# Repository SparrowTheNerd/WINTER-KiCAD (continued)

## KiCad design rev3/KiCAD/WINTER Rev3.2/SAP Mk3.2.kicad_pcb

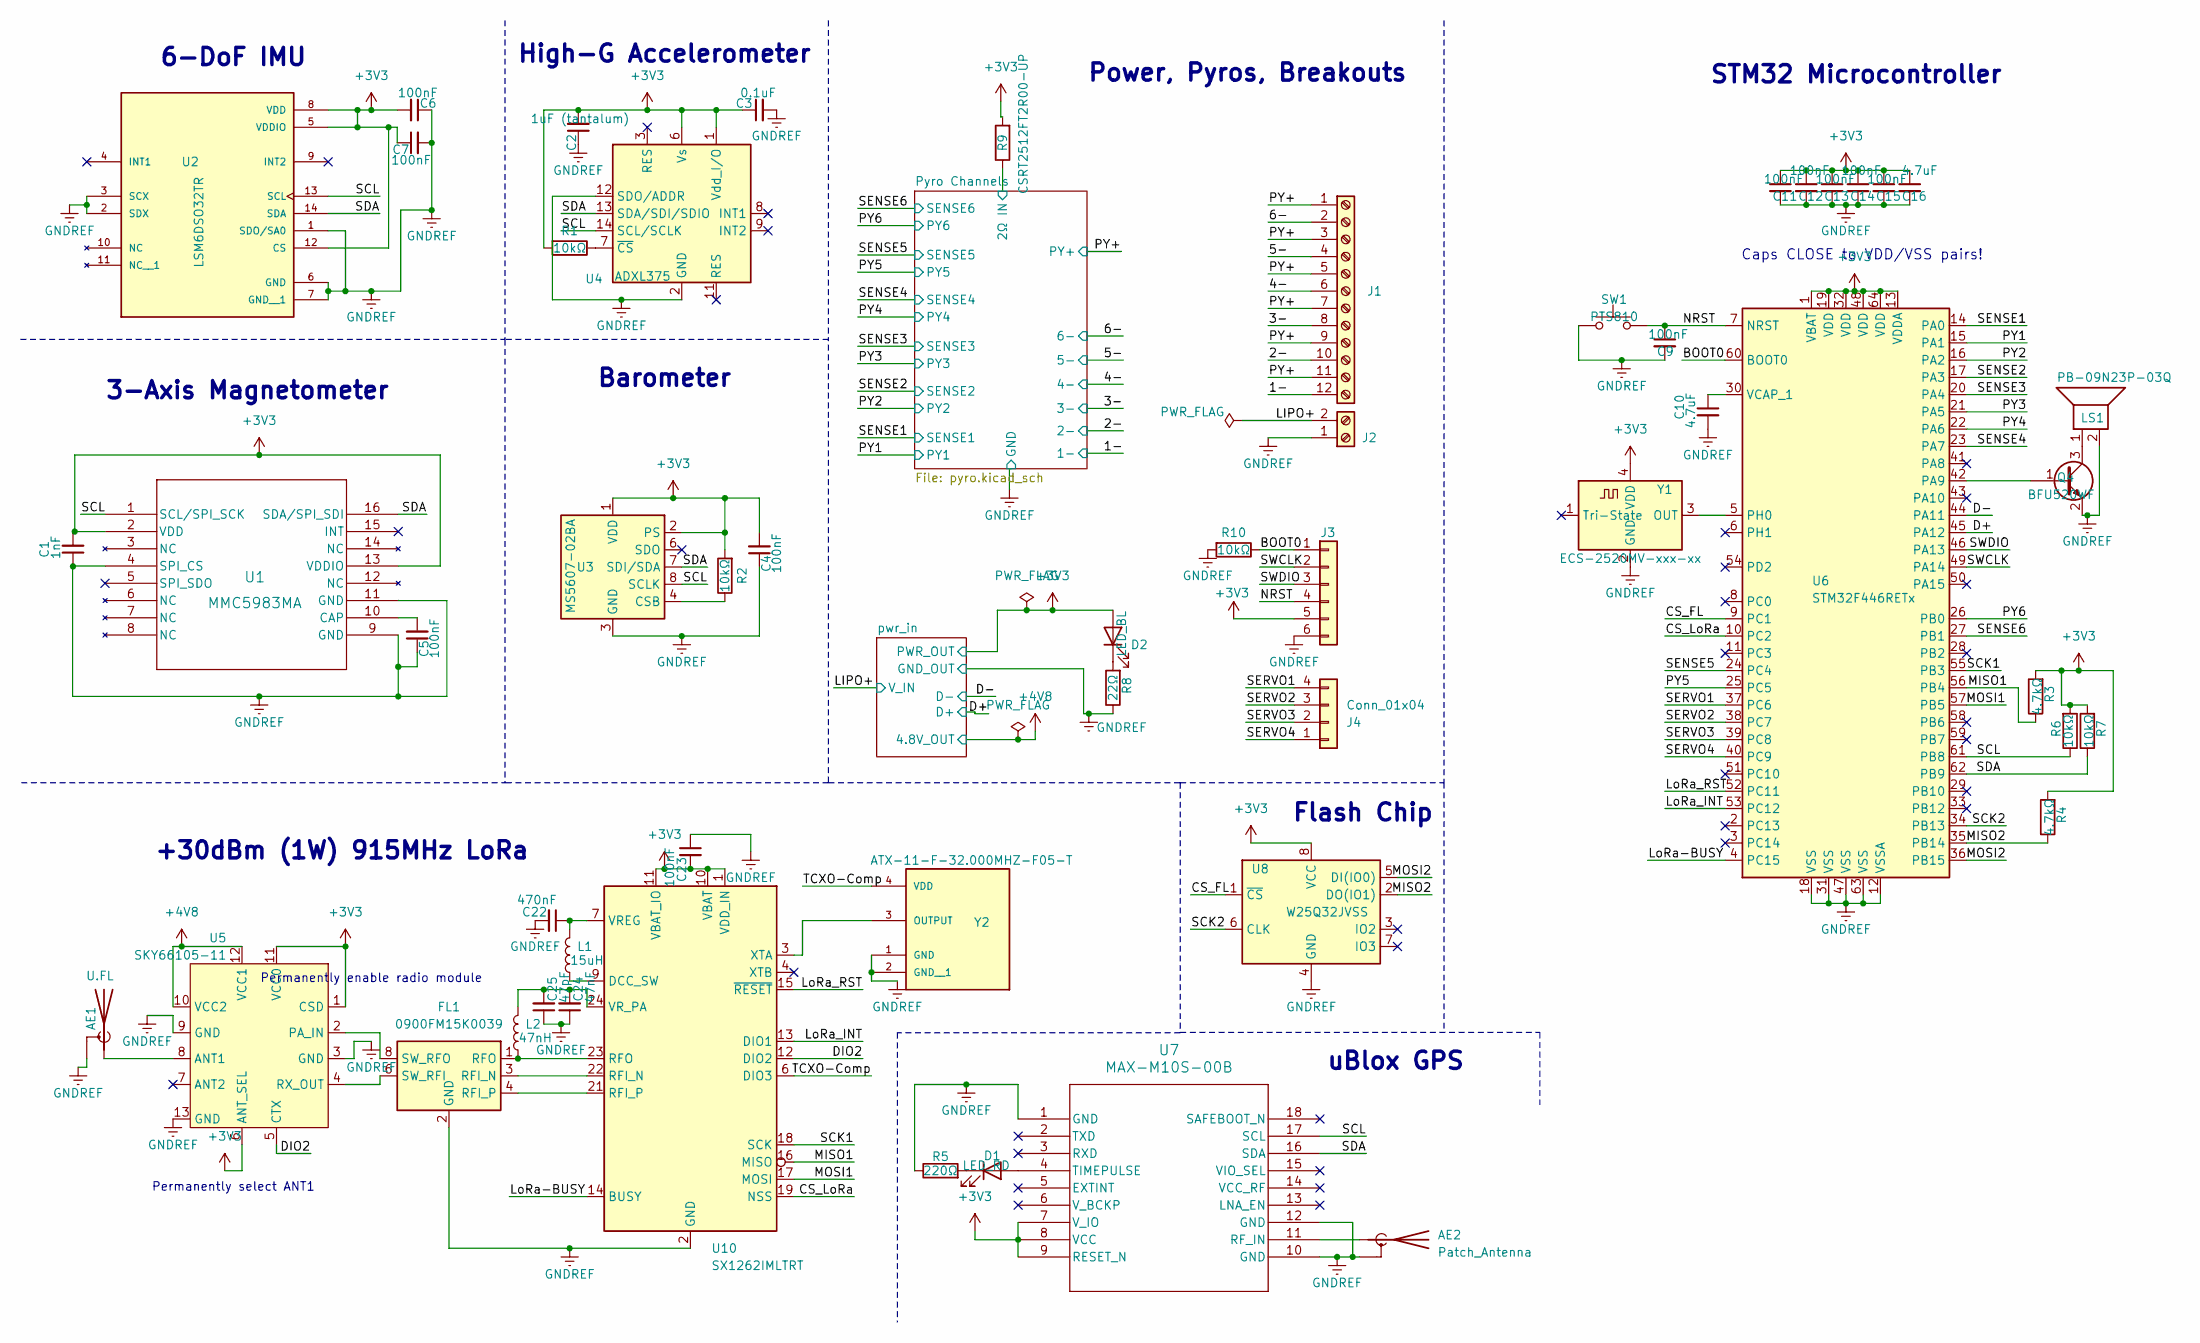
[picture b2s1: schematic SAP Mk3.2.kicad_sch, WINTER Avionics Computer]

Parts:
AE1: U.FL; U.FL_Molex_MCRF_73412-0110_Vertical
AE2: Patch_Antenna; TAOGLAS SGGP.12.4.A.02
C1: 1nF; C_0603_1608Metric
C2: 1uF (tantalum); C_0603_1608Metric
C3: 0.1uF; C_0603_1608Metric
C4, C5, C6, C7, C9, C11, C12, C13, C14, C15, C23: 100nF; C_0603_1608Metric
C10, C16: 4.7uF; C_0603_1608Metric
C22: 470nF; C_0603_1608Metric
C24: 47nF; C_0201_0603Metric
C25: 47pF; C_0201_0603Metric
D1: LED_RD; LED_0603_1608Metric
D2: LED_BL; LED_0603_1608Metric
FL1: 0900FM15K0039; Balun_Johanson_0900FM15K0039
J1: Screw_Terminal_01x12; TerminalBlock_Phoenix_MPT-0,5-12-2.54_1x12_P2.54mm_Horizont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
J2: Screw_Terminal_01x02; PinHeader_1x02_P2.54mm_Vertical
J3: Conn_01x06; PinHeader_1x06_P2.54mm_Vertical
J4: Conn_01x04; PinHeader_1x04_P2.54mm_Vertical
L1: 15uH; L_0805_2012Metric
L2: 47nH; L_0402_1005Metric
LS1: PB-09N23P-03Q; MagneticBuzzer_ProSignal_ABT-410-RC
Q4: BFU520WF; SOT-323_SC-70
R1, R2, R6, R7, R10: 10kΩ; R_0603_1608Metric
R3, R4: 4.7kΩ; R_0603_1608Metric
R5: 220Ω; R_0603_1608Metric
R8: 22Ω; R_0603_1608Metric
R9: CSRT2512FT2R00-UP; R_2512_6332Metric
SW1: PTS810; SW_SPST_PTS810
U1: MMC5983MA; MMC5983MA_MEM
U2: LSM6DSO32TR; PARTREV 1
U3: MS5607-02BA; LGA-8_3x5mm_P1.25mm
U4: ADXL375; LGA-14_3x5mm_P0.8mm_LayoutBorder1x6y
U5: SKY66105-11
U6: STM32F446RETx; LQFP-64_10x10mm_P0.5mm
U7: MAX-M10S-00B
U8: W25Q32JVSS; SOIC-8_5.23x5.23mm_P1.27mm
U10: SX1262IMLTRT; QFN-24-1EP_4x4mm_P0.5mm_EP2.6x2.6mm
Y1: ECS-2520MV-xxx-xx; Oscillator_SMD_ECS_2520MV-xxx-xx-4Pin_2.5x2.0mm
Y2: ATX-11-F-32.000MHZ-F05-T; OSC_ATX-11-F-32.000MHZ-F05-T; PARTREV 11-11-20

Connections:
+3V3: C1.2, C2.2, C3.1, C4.2, C6.2, C7.1, C11.1, C12.1, C13.1, C14.1, C15.1, C16.1, C23.2, D2.2 (A), J3.5, R1.2, R2.2, R3.2, R4.2, R6.2, R7.2, R9.2, U1.2 (VDD), U1.13 (VDDIO), U2.5 (VDDIO), U2.8 (VDD), U2.12 (CS), U3.1 (VDD), U3.2 (PS), U4.1 (Vdd_I/O), U4.6 (Vs), U5.1 (CSD), U5.6 (ANT_SEL), U5.11 (VCC0), U6.1 (VBAT), U6.13 (VDDA), U6.19 (VDD), U6.32 (VDD), U6.48 (VDD), U6.64 (VDD), U7.7 (V_IO), U7.8 (VCC), U7.9 (RESET_N), U8.8 (VCC), U10.1 (VDD_IN), U10.10 (VBAT), U10.11 (VBAT_IO), Y1.4 (VDD); also elsewhere on the board
+4V8: U5.10 (VCC2), U5.12 (VCC1); also elsewhere on the board
/1-: J1.12; also elsewhere on the board
/2-: J1.10; also elsewhere on the board
/3-: J1.8; also elsewhere on the board
/4-: J1.6; also elsewhere on the board
/5-: J1.4; also elsewhere on the board
/6-: J1.2; also elsewhere on the board
/BOOT0: J3.1, R10.1, U6.60 (BOOT0)
/CS_FL: U6.9 (PC1), U8.1 (~CS)
/CS_LoRa: U6.10 (PC2), U10.19 (NSS)
/D+: U6.45 (PA12); also elsewhere on the board
/D-: U6.44 (PA11); also elsewhere on the board
/DIO2: U5.5 (CTX), U10.12 (DIO2)
/LIPO+: J2.2; also elsewhere on the board
/LoRa-BUSY: U6.4 (PC15), U10.14 (BUSY)
/LoRa_INT: U6.53 (PC12), U10.13 (DIO1)
/LoRa_RST: U6.52 (PC11), U10.15 (~RESET)
/MISO1: R3.1, U6.56 (PB4), U10.16 (MISO)
/MISO2: R4.1, U6.35 (PB14), U8.2 (DO(IO1))
/MOSI1: U6.57 (PB5), U10.17 (MOSI)
/MOSI2: U6.36 (PB15), U8.5 (DI(IO0))
/NRST: C9.1, J3.4, SW1.2 (B), U6.7 (NRST)
/PY1: U6.15 (PA1); also elsewhere on the board
/PY2: U6.16 (PA2); also elsewhere on the board
/PY3: U6.21 (PA5); also elsewhere on the board
/PY4: U6.22 (PA6); also elsewhere on the board
/PY5: U6.25 (PC5); also elsewhere on the board
/PY6: U6.26 (PB0); also elsewhere on the board
/PY+: J1.1, J1.3, J1.5, J1.7, J1.9, J1.11, R9.1
/SCK1: U6.55 (PB3), U10.18 (SCK)
/SCK2: U6.34 (PB13), U8.6 (CLK)
/SCL: R6.1, U1.1 (SCL/SPI_SCK), U2.13 (SCL), U3.8 (SCLK), U4.14 (SCL/SCLK), U6.61 (PB8), U7.17 (SCL)
/SDA: R7.1, U1.16 (SDA/SPI_SDI), U2.14 (SDA), U3.7 (SDI/SDA), U4.13 (SDA/SDI/SDIO), U6.62 (PB9), U7.16 (SDA)
/SENSE1: U6.14 (PA0); also elsewhere on the board
/SENSE2: U6.17 (PA3); also elsewhere on the board
/SENSE3: U6.20 (PA4); also elsewhere on the board
/SENSE4: U6.23 (PA7); also elsewhere on the board
/SENSE5: U6.24 (PC4); also elsewhere on the board
/SENSE6: U6.27 (PB1); also elsewhere on the board
/SERVO1: J4.4, U6.37 (PC6)
/SERVO2: J4.3, U6.38 (PC7)
/SERVO3: J4.2, U6.39 (PC8)
/SERVO4: J4.1, U6.40 (PC9)
/SWCLK: J3.2, U6.49 (PA14)
/SWDIO: J3.3, U6.46 (PA13)
/TCXO-Comp: U10.6 (DIO3), Y2.4 (VDD)
GNDREF: AE1.2 (Shield), AE2.1 (Shield), C1.1, C2.1, C3.2, C4.1, C5.1, C6.1, C7.2, C9.2, C10.2, C11.2, C12.2, C13.2, C14.2, C15.2, C16.2, C22.2, C23.1, C24.1, C25.1, FL1.2 (GND), FL1.5 (GND), FL1.7 (GND), FL1.9 (GND), FL1.10 (GND), J2.1, J3.6, LS1.2, Q4.2 (E), R5.1, R8.1, R10.2, SW1.1 (A), U1.4 (SPI_CS), U1.9 (GND), U1.11 (GND), U2.1 (SDO/SA0), U2.2 (SDX), U2.3 (SCX), U2.6 (GND), U2.7 (GND__1), U3.3 (GND), U4.2 (GND), U4.4 (GND), U4.5 (GND), U4.12 (SDO/ADDR), U5.3 (GND), U5.9 (GND), U5.13 (GND), U6.12 (VSSA), U6.18 (VSS), U6.31 (VSS), U6.47 (VSS), U6.63 (VSS), U7.1 (GND), U7.10 (GND), U7.12 (GND), U8.4 (GND), U10.2 (GND), U10.5 (GND), U10.8 (GND), U10.20 (GND), U10.25 (GND), Y1.2 (GND), Y2.1 (GND), Y2.2 (GND__1); also elsewhere on the board
unnamed: AE1.1 (A), U5.8 (ANT1)
unnamed: AE2.2 (A), U7.11 (RF_IN)
unnamed: D1.2 (A), U7.4 (TIMEPULSE)
unnamed: D1.1 (K), R5.2
unnamed: D2.1 (K), R8.2
unnamed: FL1.3 (RFI_N), U10.22 (RFI_N)
unnamed: FL1.4 (RFI_P), U10.21 (RFI_P)
unnamed: FL1.1 (RFO), L2.1, U10.23 (RFO)
unnamed: FL1.6 (SW_RFI), U5.4 (RX_OUT)
unnamed: FL1.8 (SW_RFO), U5.2 (PA_IN)
unnamed: Q4.1 (B), U6.42 (PA9)
unnamed: LS1.1, Q4.3 (C)
unnamed: R2.1, U3.4 (CSB), U3.5 (CSB)
unnamed: C5.2, U1.10 (CAP)
unnamed: R1.1, U4.7 (~CS)
unnamed: U6.5 (PH0), Y1.3 (OUT)
unnamed: C10.1, U6.30 (VCAP_1)
unnamed: L1.1, U10.9 (DCC_SW)
unnamed: C22.1, L1.2, U10.7 (VREG)
unnamed: C24.2, C25.2, L2.2, U10.24 (VR_PA)
unnamed: U10.3 (XTA), Y2.3 (OUTPUT)

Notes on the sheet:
6-DoF IMU
Flash Chip
Barometer
Permanently select ANT1
Permanently enable radio module
+30dBm (1W) 915MHz LoRa
Caps CLOSE to VDD/VSS pairs!
High-G Accelerometer
uBlox GPS
Power, Pyros, Breakouts
3-Axis Magnetometer
STM32 Microcontroller

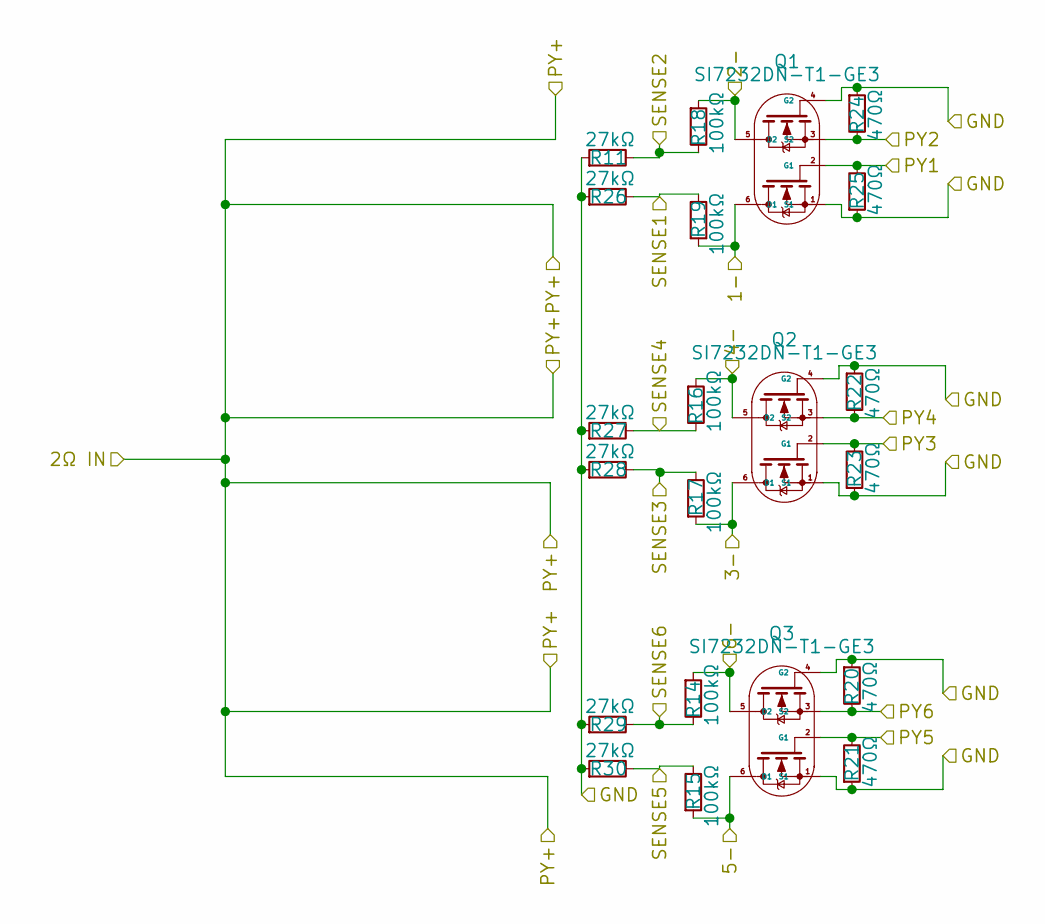
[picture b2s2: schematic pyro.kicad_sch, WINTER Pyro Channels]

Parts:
Q1, Q2, Q3: SI7232DN-T1-GE3; TRANS_SI7232DN-T1-GE3
R11, R26, R27, R28, R29, R30: 27kΩ; R_0603_1608Metric
R14, R15, R16, R17, R18, R19: 100kΩ; R_0603_1608Metric
R20, R21, R22, R23, R24, R25: 470Ω; R_0603_1608Metric

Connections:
/1-: Q1.6 (D1), R19.1; also elsewhere on the board
/2-: Q1.5 (D2), R18.1; also elsewhere on the board
/3-: Q2.6 (D1), R17.1; also elsewhere on the board
/4-: Q2.5 (D2), R16.1; also elsewhere on the board
/5-: Q3.6 (D1), R15.1; also elsewhere on the board
/6-: Q3.5 (D2), R14.1; also elsewhere on the board
/PY1: Q1.2 (G1), R25.2; also elsewhere on the board
/PY2: Q1.3 (S2), R24.2; also elsewhere on the board
/PY3: Q2.2 (G1), R23.2; also elsewhere on the board
/PY4: Q2.3 (S2), R22.2; also elsewhere on the board
/PY5: Q3.2 (G1), R21.2; also elsewhere on the board
/PY6: Q3.3 (S2), R20.2; also elsewhere on the board
/SENSE1: R19.2, R26.2; also elsewhere on the board
/SENSE2: R11.2, R18.2; also elsewhere on the board
/SENSE3: R17.2, R28.2; also elsewhere on the board
/SENSE4: R16.2, R27.2; also elsewhere on the board
/SENSE5: R15.2, R30.2; also elsewhere on the board
/SENSE6: R14.2, R29.2; also elsewhere on the board
GNDREF: Q1.1 (S1), Q1.4 (G2), Q2.1 (S1), Q2.4 (G2), Q3.1 (S1), Q3.4 (G2), R11.1, R20.1, R21.1, R22.1, R23.1, R24.1, R25.1, R26.1, R27.1, R28.1, R29.1, R30.1; also elsewhere on the board

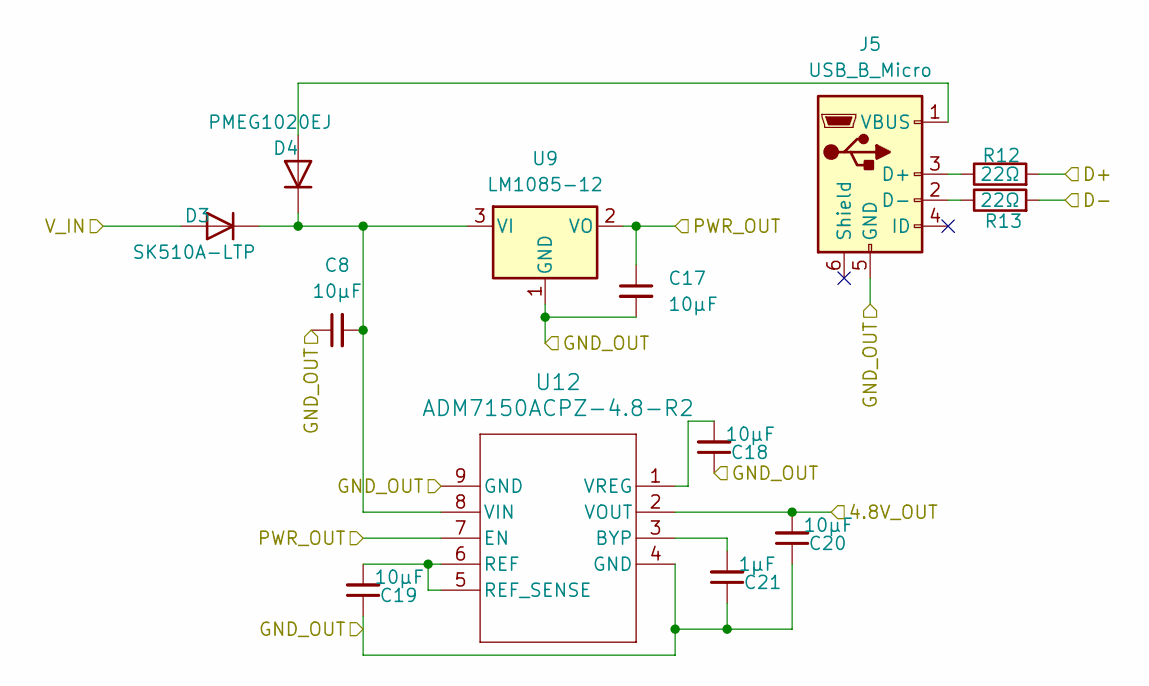
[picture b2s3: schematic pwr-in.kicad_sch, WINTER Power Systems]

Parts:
C8, C17, C18, C19, C20: 10µF; C_0603_1608Metric
C21: 1µF; C_0603_1608Metric
D3: SK510A-LTP; D_SMA
D4: PMEG1020EJ; D_SOD-323F
J5: USB_B_Micro; USB_Micro-B_GCT_USB3076-30-A
R12, R13: 22Ω; R_0603_1608Metric
U9: LM1085-12; TO-220-3_Vertical
U12: ADM7150ACPZ-4.8-R2; CP-8-11_ADI

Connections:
+3V3: C17.1, U9.2 (VO), U12.7 (EN); also elsewhere on the board
+4V8: C20.2, U12.2 (VOUT); also elsewhere on the board
/D+: R12.2; also elsewhere on the board
/D-: R13.2; also elsewhere on the board
/LIPO+: D3.2 (A); also elsewhere on the board
GNDREF: C8.1, C17.2, C18.1, C19.1, C20.1, C21.1, J5.5 (GND), U9.1 (GND), U12.4 (GND), U12.9 (GND); also elsewhere on the board
unnamed: C8.2, D3.1 (K), D4.1 (K), U9.3 (VI), U12.8 (VIN)
unnamed: D4.2 (A), J5.1 (VBUS)
unnamed: J5.3 (D+), R12.1
unnamed: J5.2 (D-), R13.1
unnamed: C21.2, U12.3 (BYP)
unnamed: C19.2, U12.5 (REF_SENSE), U12.6 (REF)
unnamed: C18.2, U12.1 (VREG)

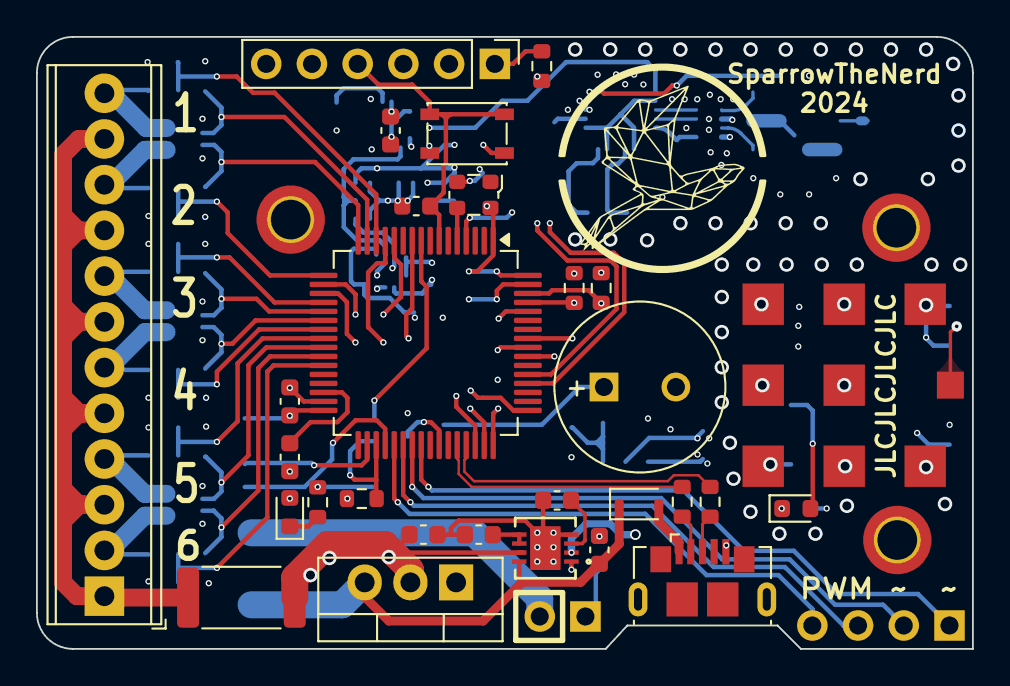
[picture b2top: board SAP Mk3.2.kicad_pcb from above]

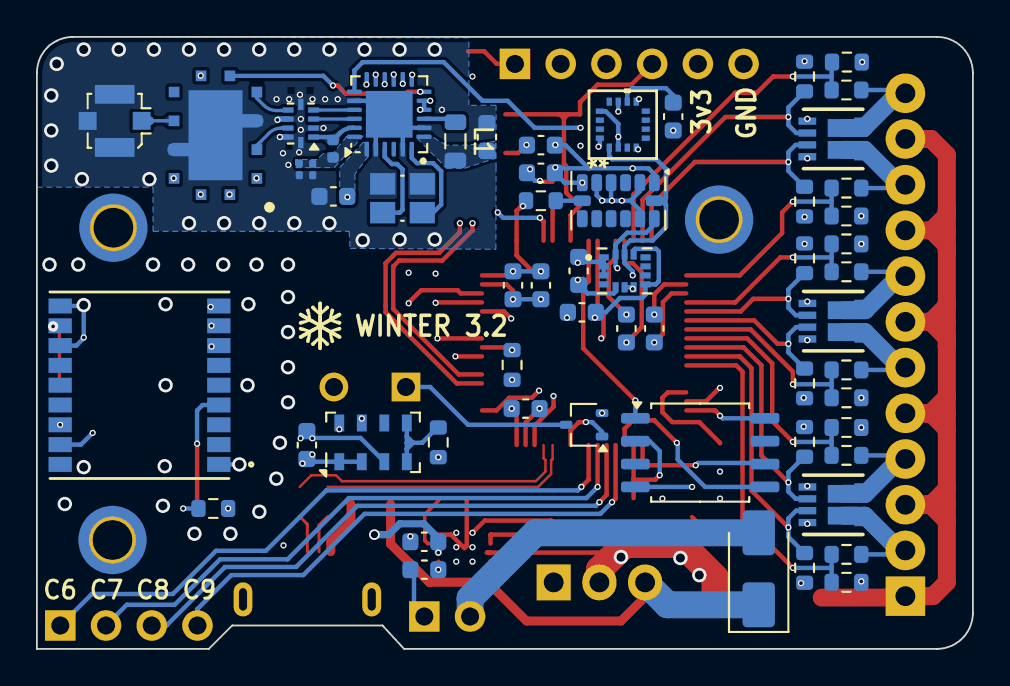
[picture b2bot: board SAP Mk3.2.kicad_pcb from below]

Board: 8 copper layers, 52.0 x 34.0 mm, 88 parts (57 on the bottom side), 76 nets.

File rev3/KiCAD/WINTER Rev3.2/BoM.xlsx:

Reference | Value | Footprint | Qty | Distributor | Product ID | Price Per Item | Price |  | Cost: | 84.72999999999999
AE1 | U.FL | Connector_Coaxial:U.FL_Molex_MCRF_73412-0110_Vertical | 1 | Digi-Key | CONUFL001-SMD-T | 0.44 | 0.44
AE2 | Patch_Antenna | TAOGLAS SGGP.12.4.A.02 | 1 | Digi-Key | SGGP.12.4.A.02 | 6.78 | 6.78
C1 | 1nF | C_0603_1608Metric | 1 | Digi-Key | CL10C102JB8NNNC | 0.1 | 0.1
C2 | 1uF (tantalum) | C_0603_1608Metric | 1 | Digi-Key | TACL105K016RTA | 1.75 | 1.75
C3,C4,C5,C6,C7,C9,C11,C12,C13,C14,C15,C23 | 0.1uF | C_0603_1608Metric | 12 | Digi-Key | CL10B104JB8NNNC | 0.1 | 1.2000000000000002
C8,C17,C18,C19,C20 | 10µF | C_0603_1608Metric | 5 | Digi-Key | CL10A106KQ8NNNC | 0.13 | 0.65
C10,C16 | 4.7uF | C_0603_1608Metric | 2 | Digi-Key | CL10A475KP8NNNC | 0.1 | 0.2
C21 | 1µF | C_0603_1608Metric | 1 | Digi-Key | CL10B105KP8NNNC | 0.1 | 0.1
C22 | 470nF | C_0603_1608Metric | 1 | Digi-Key | CL10B474KA8NFNC | 0.1 | 0.1
C24 | 47nF | C_0201_0603Metric | 1 | Digi-Key | 490-GRM033R60J473JE19DCT-ND | 0.1 | 0.1
C25 | 47pF | C_0201_0603Metric | 1 | Digi-Key | CL10C470JB8NNNC | 0.1 | 0.1
D1 | LED_RD | LED_SMD:LED_0603_1608Metric | 1 | Digi-Key | LTST-C191KRKT | 0.26 | 0.26
D2 | LED_BL | LED_SMD:LED_0603_1608Metric | 1 | Digi-Key | LTST-C191TBKT | 0.34 | 0.34
D3 | SK510A-LTP | Diode_SMD:D_SMA | 1 | Digi-Key | SK510A-LTP | 0.35 | 0.35
D4 | PMEG1020EJ | Diode_SMD:D_SOD-323F | 1 | Digi-Key | PMEG1020EJ,115 | 0.43 | 0.43
FL1 | 0900FM15D0039 | RF_Converter:Balun_Johanson_0900FM15K0039 | 1 | Digi-Key | 0900FM15D0039 | 0.47 | 0.47
J1 | Screw_Terminal_01x12 | TerminalBlock_Phoenix:TerminalBlock_Phoenix_MPT-0,5-12-2.54_1x12_P2.54mm_Horizo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 | 1 | Digi-Key | OSTVN12A150 | 3.75 | 3.75
J2 | Screw_Terminal_01x02 | Connector_PinHeader_2.54mm:PinHeader_1x02_P2.54mm_Vertical | 1 |  | DNP | 0 | 0
J3 | Conn_01x06 | Connector_PinHeader_2.54mm:PinHeader_1x06_P2.54mm_Vertical | 1 |  | OWNED |  | 0
J4 | Conn_01x04 | Connector_PinHeader_2.54mm:PinHeader_1x04_P2.54mm_Vertical | 1 |  | OWNED |  | 0
J5 | USB_B_Micro | Connector_USB:USB_Micro-B_GCT_USB3076-30-A | 1 |  | OWNED |  | 0
L1 | 15uH | Inductor_SMD:L_0805_2012Metric | 1 | Digi-Key | MLZ2012M150WT000 | 0.12 | 0.12
L2 | 47nH | Inductor_SMD:L_0402_1005Metric | 1 | Digi-Key | LQW15AN47NJ80D | 0.19 | 0.19
LS1 | PB-09N23P-03Q | Buzzer_Beeper:MagneticBuzzer_ProSignal_ABT-410-RC | 1 | Digi-Key | PB-09N23P-03Q | 2.0099999999999998 | 2.0099999999999998
Q1,Q2,Q3 | SI7232DN-T1-GE3 | TRANS_SI7232DN-T1-GE3 | 3 | Digi-Key | SI7232DN-T1-GE3 | 0.87 | 2.61
Q4 | BFU520WF | TO_SOT_SMD:SOT-323_SC-70 | 1 | Digi-Key | BFU520WF | 0.5 | 0.5
R1,R2,R6,R7,R10 | 10kΩ | R_0603_1608Metric | 5 | Digi-Key | OWNED |  | 0
R3,R4 | 4.7kΩ | R_0603_1608Metric | 2 | Digi-Key | OWNED |  | 0
R5 | 220Ω | R_0603_1608Metric | 1 | Digi-Key | CRGCQ0603J220R | 0.1 | 0.1
R8,R12,R13 | 22Ω | R_0603_1608Metric | 3 | Digi-Key | OWNED |  | 0
R9 | CSRT2512FT2R00-UP | R_2512_6332Metric | 1 | Digi-Key | CSRT2512FT2R00-UP | 0.68 | 0.68
R11,R26,R27,R28,R29,R30 | 27kΩ | R_0603_1608Metric | 6 | Digi-Key | RMCF0603JT27K0CT-ND | 0.1 | 0.60000000000000009
R14,R15,R16,R17,R18,R19 | 100kΩ | R_0603_1608Metric | 6 | Digi-Key | RMCF0603FT100KCT-ND | 0.1 | 0.60000000000000009
R20,R21,R22,R23,R24,R25 | 470Ω | R_0603_1608Metric | 6 | Digi-Key | OWNED |  | 0
SW1 | PTS810 | Button_Switch_SMD:SW_SPST_PTS810 | 1 |  | OWNED |  | 0
U1 | MMC5983MA | MMC5983MA_MEM | 1 | Digi-Key | MMC5983MA | 3.6 | 3.6
U2 | LSM6DSO32TR | LSM6DSO32TR | 1 | Digi-Key | OWNED |  | 0
U3 | MS5607-02BA | LGA:LGA-8_3x5mm_P1.25mm | 1 |  | OWNED |  | 0
U4 | ADXL375 | LGA:LGA-14_3x5mm_P0.8mm_LayoutBorder1x6y | 1 | Digi-Key | OWNED |  | 0
U5 | SKY66105-11 | SKY66105-11 | 1 | Digi-Key | SKY66105-11 | 5.3 | 5.3
U6 | STM32F446RETx | QFP:LQFP-64_10x10mm_P0.5mm | 1 | Digi-Key | STM32F446RET6 | 10.050000000000001 | 10.050000000000001
U7 | MAX-M10S-00B | MAX-M10S-00B | 1 | Digi-Key | MAX-M10S-00B | 21 | 21
U8 | W25Q32JVSS | SO:SOIC-8_5.23x5.23mm_P1.27mm | 1 |  | OWNED |  | 0
U9 | LM1085-3.3 | TO_SOT_THT:TO-220-3_Vertical | 1 | Digi-Key | LM1085IT-3.3/NOPB | 1.99 | 1.99
U10 | SX1262IMLTRT | DFN_QFN:QFN-24-1EP_4x4mm_P0.5mm_EP2.6x2.6mm | 1 | Digi-Key | SX1262IMLTRT | 7.99 | 7.99
U12 | ADM7150ACPZ-4.8-R2 | CP-8-11_ADI | 1 | Digi-Key | ADM7150ACPZ-4.8-R2 | 7.6 | 7.6
Y1 | ECS-2520MV-xxx-xx | Oscillator:Oscillator_SMD_ECS_2520MV-xxx-xx-4Pin_2.5x2.0mm | 1 | Digi-Key | OWNED |  | 0
Y2 | ATX-11-F-32.000MHZ-F05-T | OSC_ATX-11-F-32.000MHZ-F05-T | 1 | Digi-Key | 535-ATX-11-F-32.000MHZ-F05-TCT-ND | 2.67 | 2.67

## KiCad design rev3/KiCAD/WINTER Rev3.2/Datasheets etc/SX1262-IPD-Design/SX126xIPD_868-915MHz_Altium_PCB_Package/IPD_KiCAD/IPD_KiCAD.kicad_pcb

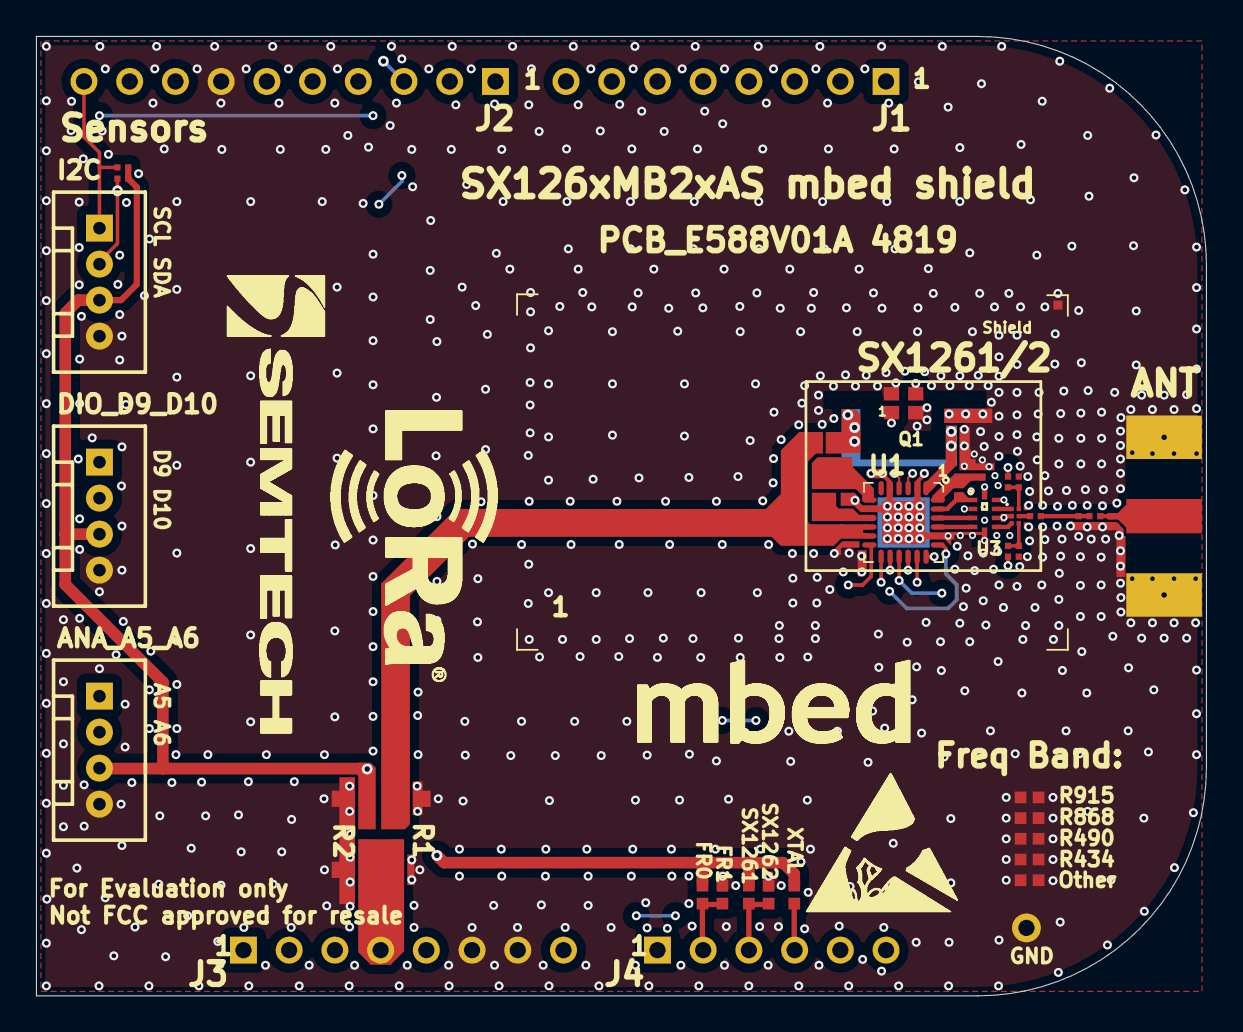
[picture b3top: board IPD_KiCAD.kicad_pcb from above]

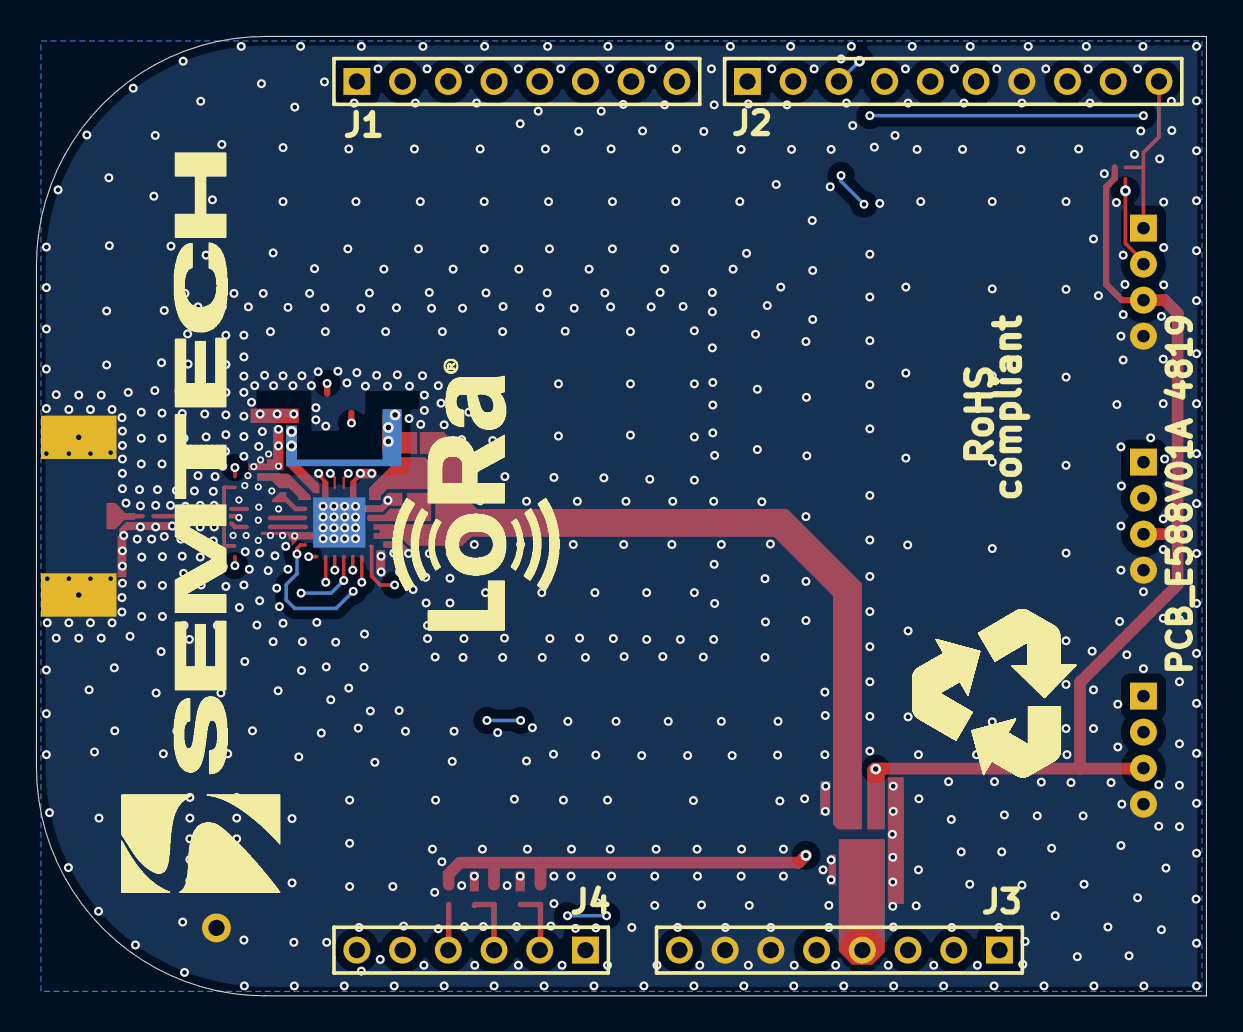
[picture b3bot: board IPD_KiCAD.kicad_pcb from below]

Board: 4 copper layers, 65.0 x 53.3 mm, 56 parts (7 on the bottom side), 38 nets.

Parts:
ANA_A5_A6: Header 4; 1125S-4P_connector
ANT: SMA; SMA_end_launch_1.0mm_9.52mm
C1, C9, C10: Cap; rlc_201_smd
C2, C8, C14, C15, C18, C23: Cap; RLC_201_SMD
C16, C17: Cap; rlc_402_smd_small
C20, C21, C22: Cap; RLC_603_SMD
DIO_D9_D10: Header 4; 1125S-4P_connector
FR0, FR1: Resistor; RLC_402_SMD
GND: Test Pin; pin_0.9mm
I2C: Header 4; 1125S-4P_connector
J1, J3: Header 8; HDR1X8
J2: Header 10; HDR1X10
J4: Header 6; HDR1X6
L1, L8: Inductor; rlc_402_smd_small
L5: Inductor; rlc_201_smd
L7: Inductor; rlc_805_smd_small
Logo Bot1: Logo symbol; Logo LoRa Size4
Logo ESD1: Logo symbol; Logo ESD
Logo Recycling1: Logo symbol; Logo Recycling1
Logo Semtech_1: Logo symbol; logo_semtech_horiz_size3
Logo_LoRA_Top1: Logo symbol; Logo LoRa Size4
Logo_Semtech1: Logo symbol; logo_semtech_horiz_size4
Logo_mbed1: Logo symbol; logo mbed 2
Other: Resistor; RLC_402_SMD
Q1: Xtal; nd2016da
R1, R2: Resistor; RLC_603_SMD
R3, R4, R5, R6: Resistor; RLC_201_SMD
R18: Resistor; rlc_402_smd_small
R434, R490, R868, R915: Resistor; RLC_402_SMD
SX1261, SX1262: Resistor; RLC_402_SMD
Shield: Logo symbol; BMIS-209-F - Shield
U1: SX1261/2; VQFN24_4X4MM
U2: BGS12SN6 RF Switch; TSNP-6-2
U3: 0900FM15D0039; IPD FILTER
XTAL: Resistor; RLC_402_SMD

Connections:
A5: ANA_A5_A6.1, J4.5
A6: ANA_A5_A6.2, J4.6
ANT_SW: J2.1, R3.2
BUSY: J1.4, U1.14
D9: DIO_D9_D10.1, J2.2
D10: DIO_D9_D10.2, J2.3
DIO1: J1.6, U1.13
DIO2: R4.2, U1.12
GND: ANA_A5_A6.4, ANT.2, C1.1, C2.1, C9.1, C10.1, C14.2, C15.2, C16.1, C17.1, C18.1, C20.1, C21.1, C22.1, C23.1, DIO_D9_D10.4, FR1.1, GND.1, I2C.4, J2.7, J3.6, J3.7, Other.1, Other.2, Q1.2, Q1.4, R434.1, R434.2, R490.1, R490.2, R868.1, R868.2, R915.1, R915.2, SX1262.1, Shield.1, U1.2, U1.5, U1.8, U1.20, U1.25, U2.2, U3.2, U3.5, U3.7, U3.9, U3.10
I2C_SCL: I2C.1, J2.10, R6.1
I2C_SDA: I2C.2, J2.9, R5.1
MISO: J2.5, U1.16
MOSI: J2.4, U1.17
NSS: J1.8, U1.19
NetANT_1: ANT.1, C10.2, L5.2
NetC8_1: C8.1, C9.2, L5.1
NetC8_2: C8.2, U2.5
NetC14_1: C14.1, R4.1, U2.6
NetC15_1: C15.1, R3.1, U2.4
NetC16_2: C16.2, L8.1, R18.1, U1.1
NetC17_2: C17.2, L7.1, L8.2, U1.7
NetFR0_2: FR0.2, FR1.2, J4.2
NetJ4_3: J4.3, SX1261.2, SX1262.2
NetL1_1: L1.1, U1.23, U3.1
NetL7_2: L7.2, U1.9
NetU1_21: U1.21, U3.4
NetU1_22: U1.22, U3.3
NetU2_1: U2.1, U3.8
NetU2_3: U2.3, U3.6
OPT: J4.4, XTAL.2
SCK: J2.6, U1.18
SX_NRESET: J4.1, U1.15
VDD_3V3: ANA_A5_A6.3, C21.2, DIO_D9_D10.3, FR0.1, I2C.3, R2.1, R5.2, R6.2, SX1261.1, XTAL.1
VDD_MBED: C22.2, C23.2, J3.4, R1.2, R2.2
VDD_RADIO: C18.2, C20.2, R1.1, R18.2, U1.10, U1.11
VR_PA: C1.2, C2.2, L1.2, U1.24
XTA: Q1.3, U1.3
XTB: Q1.1, U1.4

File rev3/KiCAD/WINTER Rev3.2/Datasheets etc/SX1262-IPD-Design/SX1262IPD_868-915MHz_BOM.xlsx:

|  |  | SX1262MB2IPDDAS mbed shield with IPD filter BOM - 868/915MHz |  |  | BOM # V1a
 |  |  |  |  |  | SCH # e588v01a
 |  |  | 44635 | EMr | Version e588v01a | PCB # e588v01a
RefDes | MPN | Geom | Value | Qty | Description | Manufacturer
U1 | SX1262IMLTRT | VQFN24 4x4mm | SX1262 | 1 | 150MHz to 960MHz Low Power Long Range Transceiver | Semtech
U2 | BGS12SN6 | TSNP-6-2 | - | 1 | Wideband RF SPDT Switch | Infineon
U3 | 0900FM15K0039 | 2.00x1.25mm | 868/915MHz | 1 | 868/915MHz Miniature Impedance-matched Filter for SX1261/62 and LLCC68 | Johanson Technology
Resistors
R1 | CRCW06030000Z0EAHP | 0603 | 0R | 1 | Thick Film Resistor ±1%, 1/4W | Vishay/Dale
R2 | CRCW06030000Z0EAHP | 0603 | 0R | 1 | Thick Film Resistor ±1%, 1/4W | Vishay/Dale
R3 | CRCW0201100RJNED | 0201 | 100R | 1 | Thick Film Resistor ±5%, 1/20W | Vishay/Dale
R4 | CRCW0201100RJNED | 0201 | 100R | 1 | Thick Film Resistor ±5%, 1/20W | Vishay/Dale
R5 | CRCW02013K30JNED | 0201 | 3.3k | 1 | Thick Film Resistor ±5%, 1/20W | Vishay/Dale
R6 | CRCW02013K30JNED | 0201 | 3.3k | 1 | Thick Film Resistor ±5%, 1/20W | Vishay/Dale
R18 | CRCW04020000Z0ED | 0402 | 0R | 1 | Thick Film Resistor ±1%, 1/16W | Vishay/Dale
R868 | CRCW04020000Z0ED | 0402 | 0R | 1 | Thick Film Resistor ±1%, 1/16W | Vishay/Dale
R915 | CRCW04020000Z0ED | 0402 | 0R | 1 | Thick Film Resistor ±1%, 1/16W | Vishay/Dale
SX1262 | CRCW040210K0FKED | 0402 | 10k | 1 | Thick Film Resistor ±1%, 1/16W | Vishay/Dale
FR1 | CRCW040210K0FKED | 0402 | 10k | 1 | Thick Film Resistor ±1%, 1/16W | Vishay/Dale
XTAL | CRCW04020000Z0ED | 0402 | 0R | 1 | Thick Film Resistor ±1%, 1/16W | Vishay/Dale
Capacitors
C1 | GRM033R61C473KE84D | 0201 | 47nF | 1 | Multilayer ceramic capacitors X5R ±10%, 16V | Murata
C2 | GRM0335C1H470JA01D | 0201 | 47pF | 1 | Multilayer ceramic capacitors COG ±5%, 50V | Murata
C8 | GRM0335C1H390JA01D | 0201 | 39pF | 1 | Multilayer ceramic capacitors COG ±5%, 50V | Murata
C9 |  | 0201 | NC | 0 |  | Murata
C10 |  | 0201 | NC | 0 |  | Murata
C14 | GRM033R71H102KA12D | 0201 | 1nF | 1 | Multilayer ceramic capacitors X7R ±10%, 50V | Murata
C15 | GRM033R71H102KA12D | 0201 | 1nF | 1 | Multilayer ceramic capacitors X7R ±10%, 50V | Murata
C16 | GRM155R61E105KA12D | 0402 | 1uF | 1 | Multilayer ceramic capacitors X5R ±10%, 10V | Murata
C17 | GRM155R61A474KE15D | 0402 | 470nF | 1 | Multilayer ceramic capacitors X5R ±10%, 10V | Murata
C18 | GRM033R61A104KE15D | 0201 | 100nF | 1 | Multilayer ceramic capacitors X5R ±10%, 10V | Murata
C20 | GRM188R61A105KA61D | 0603 | 1uF | 1 | Multilayer ceramic capacitors X5R ±10%, 10V | Murata
C21 | GRM188R61A105KA61D | 0603 | 1uF | 1 | Multilayer ceramic capacitors X5R ±10%, 10V | Murata
C22 | GRM188R61A106KE69D | 0603 | 10uF | 1 | Multilayer ceramic capacitors X5R ±10%, 10V | Murata
C23 | GRM033R61A104KE15D | 0201 | 100nF | 1 | Multilayer ceramic capacitors X5R ±10%, 10V | Murata
Inductors & Ferrites
L1 | LQW15AN47NJ00D | 0402 | 47nH | 1 | Wirewound Inductor ±5% | Murata
L5 | CRCW02010000Z0ED | 0201 | 0R | 1 | Thick Film Resistor ±5%, 1/20W | Murata
L7 | MLZ2012M150W | 0805 | 15uH | 1 | MLZ2012 Multilayer Shielded Inductor ±5% | TDK
or (2nd source) | MLZ1608N100LT000 | 0603 | 10uH | 1 | MLZ1608 Multilayer Shielded Inductor ±20% | TDK
or (2nd source) | MLZ1608N150LT000 | 0603 | 15uH | 1 | MLZ1608 Multilayer Shielded Inductor ±20% | TDK
L8 |  | 0402 | 47nH | 0 |  | Murata
Crystal & TCXO
Q1 | EXS00A-CS06465 | NX2016SA 2.0x1.6mm | 32.000MHz | 1 | Crystal unit NDK; Tol. ±10ppm, Cload=10pF, G-Senstivity=2ppb/G max | NDK
or | FTR5123-A0 | QESM09 2.0x1.6mm | 32.000MHz | - | Crystal unit Rakon; Tol. ±10ppm, Cload=10pF, G-Senstivity=2ppb/G max | Rakon
Connectors and others (or P/N equivalent)
ANT | 142-0701-841 | SMA End Launch | 50 Ohms | 1 | SMA End launch jack receptacle for PCB mount for 1.00mm PCB thickness | Cinch Connectivity Sol Johnson
J1 | 68000-108HLF | Header 1x8 | 8 pins | 1 | 8 Pins - Through hole single row male connector, Bottom side | FCI
J2 | 68000-110HLF | Header 1x10 | 10 pins | 1 | 10 Pins - Through hole single row male connector, Bottom side | FCI
J3 | 68000-108HLF | Header 1x8 | 8 pins | 1 | 8 Pins - Through hole single row male connector, Bottom side | FCI
J4 | 68000-106HLF | Header 1x6 | 6 pins | 1 | 6 Pins - Through hole single row male connector, Bottom side | FCI
ANA_A5_A6 | 1125S-4P | 4-pin - Grove | 4 pins | 0 | 2mm pitch - Grove universal 4-pin connector for sensor (SKU: 320110033), Top si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 | Shenzhen NS-Tech
DIO_D9_D10 | 1125S-4P | 4-pin - Grove | 4 pins | 0 | 2mm pitch - Grove universal 4-pin connector for sensor (SKU: 320110033), Top si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 | Shenzhen NS-Tech
I2C | 1125S-4P | 4-pin - Grove | 4 pins | 0 | 2mm pitch - Grove universal 4-pin connector for sensor (SKU: 320110033), Top si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 | Shenzhen NS-Tech
Additional or optional components
- | BMI-S-209-F | Shield | - | 0 | Standard Surface Mount Shield in two parts with BMI-S-209-C cover (optional) | Laird Technologies
Remark: components not listed in the BOM or 0 quantity, are not populated on th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
